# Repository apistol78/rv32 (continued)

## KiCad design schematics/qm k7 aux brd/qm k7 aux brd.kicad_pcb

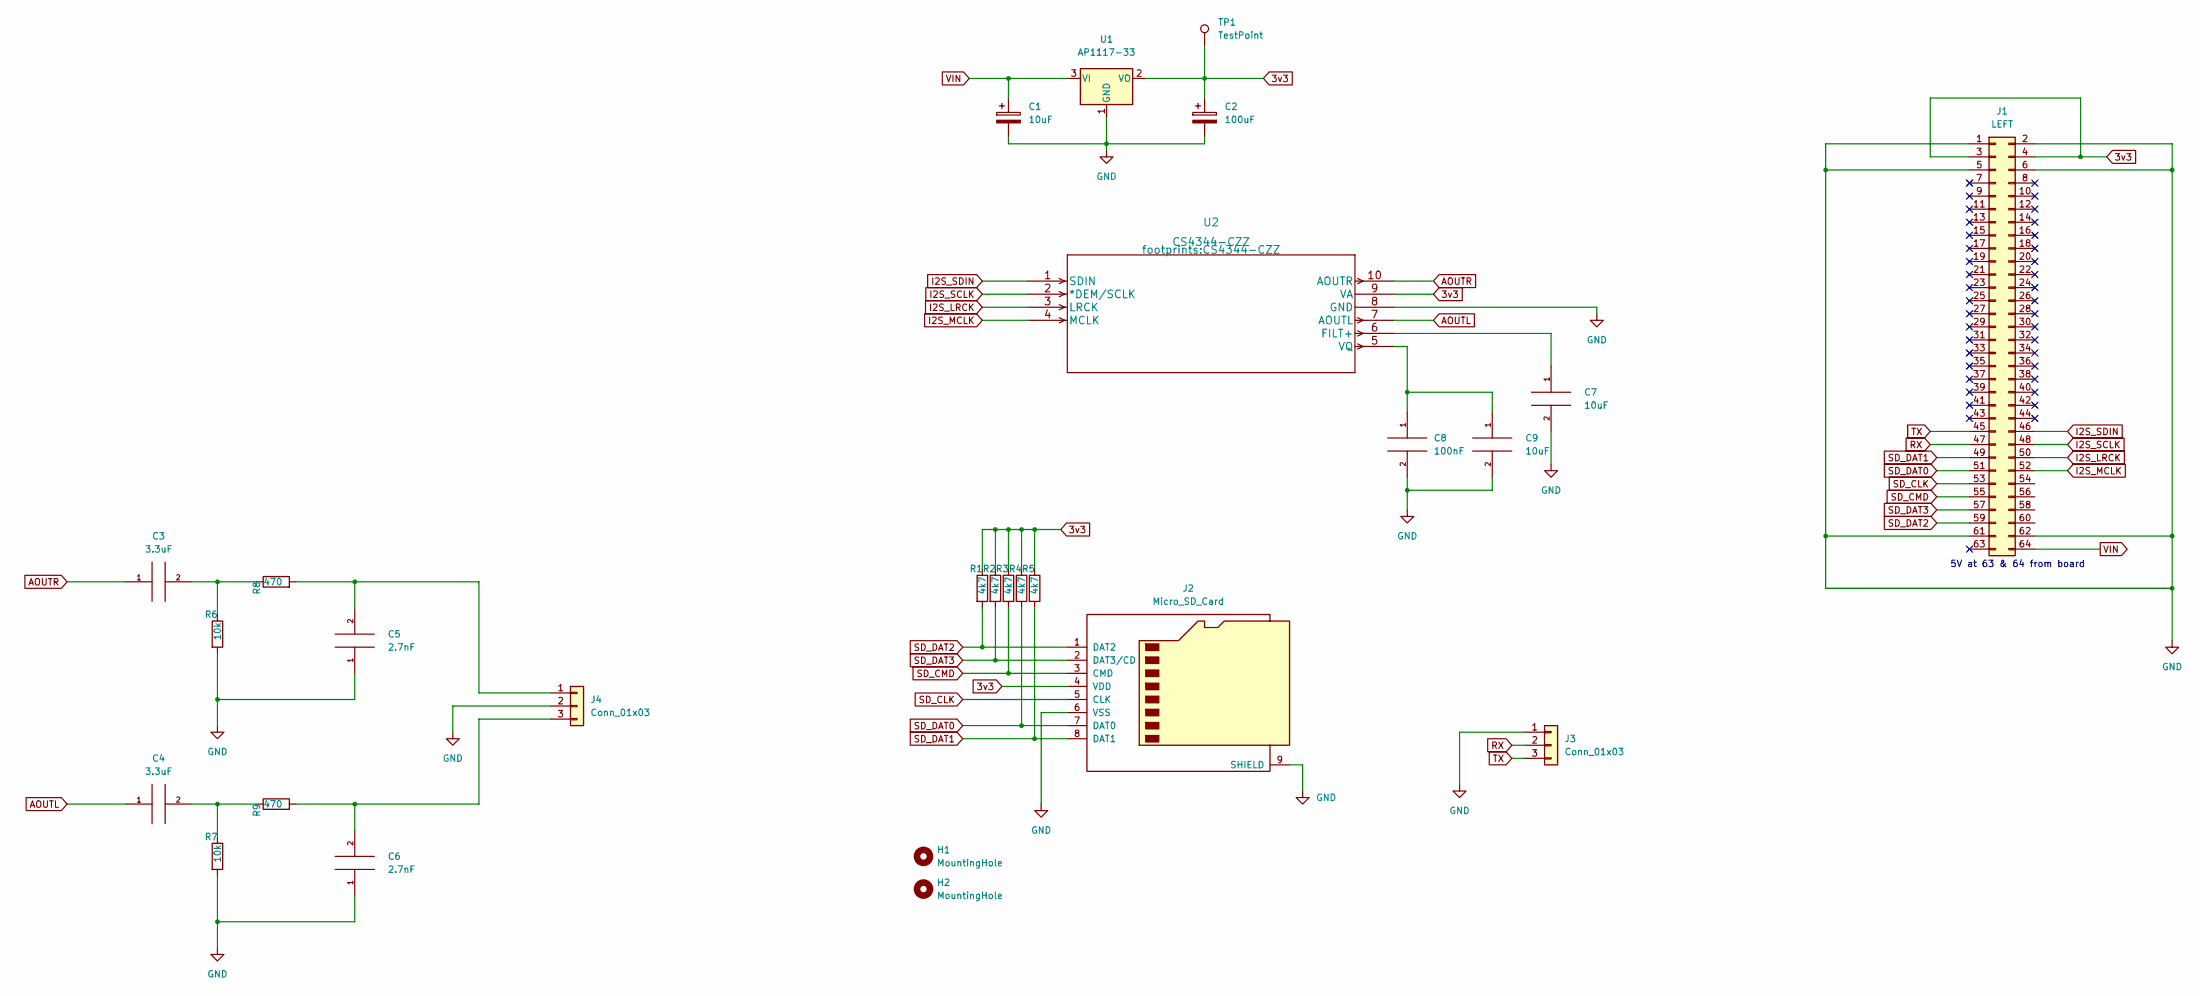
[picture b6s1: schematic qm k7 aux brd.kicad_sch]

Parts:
C1: 10uF; CP_Elec_5x5.3
C2: 100uF; CP_Elec_5x5.3
C3, C4: 3.3uF; C_0805_2012Metric_Pad1.18x1.45mm_HandSolder
C5, C6: 2.7nF; C_0805_2012Metric_Pad1.18x1.45mm_HandSolder
C7, C9: 10uF; C_0805_2012Metric_Pad1.18x1.45mm_HandSolder
C8: 100nF; C_0805_2012Metric_Pad1.18x1.45mm_HandSolder
H1, H2: MountingHole; MountingHole_3.2mm_M3_DIN965_Pad
J1: LEFT; PinSocket_2x32_P2.54mm_Vertical
J2: Micro_SD_Card; microSD_HC_Hirose_DM3D-SF
J3, J4: Conn_01x03; PinHeader_1x03_P2.54mm_Vertical
R1, R2, R3, R4, R5: 4k7; R_0805_2012Metric_Pad1.20x1.40mm_HandSolder
R6, R7: 10k; R_0805_2012Metric_Pad1.20x1.40mm_HandSolder
R8, R9: 470; R_0805_2012Metric_Pad1.20x1.40mm_HandSolder
TP1: TestPoint; TestPoint_Pad_D2.5mm
U1: AP1117-33; SOT-223-3_TabPin2
U2: CS4344-CZZ

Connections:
3v3: C2.1, J1.3, J1.4, J2.4 (VDD), R1.1, R2.1, R3.1, R4.1, R5.1, TP1.1, U1.2 (VO), U2.9 (VA)
AOUTL: C4.1, U2.7 (AOUTL)
AOUTR: C3.1, U2.10 (AOUTR)
GND: C1.2, C2.2, C5.1, C6.1, C7.2, C8.2, C9.2, J1.1, J1.2, J1.5, J1.6, J1.61, J1.62, J2.6 (VSS), J2.9 (SHIELD), J3.1, J4.2, R6.2, R7.2, U1.1 (GND), U2.8 (GND)
I2S_LRCK: J1.50, U2.3 (LRCK)
I2S_MCLK: J1.52, U2.4 (MCLK)
I2S_SCLK: J1.48, U2.2 (*DEM/SCLK)
I2S_SDIN: J1.46, U2.1 (SDIN)
unnamed: C3.2, R6.1, R8.1
unnamed: C4.2, R7.1, R9.1
unnamed: C5.2, J4.1, R8.2
unnamed: C6.2, J4.3, R9.2
unnamed: C7.1, U2.6 (FILT+)
unnamed: C8.1, C9.1, U2.5 (VQ)
RX: J1.47, J3.2
SD_CLK: J1.53, J2.5 (CLK)
SD_CMD: J1.55, J2.3 (CMD), R3.2
SD_DAT0: J1.51, J2.7 (DAT0), R4.2
SD_DAT1: J1.49, J2.8 (DAT1), R5.2
SD_DAT2: J1.59, J2.1 (DAT2), R1.2
SD_DAT3: J1.57, J2.2 (DAT3/CD), R2.2
TX: J1.45, J3.3
VIN: C1.1, J1.64, U1.3 (VI)

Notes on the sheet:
5V at 63 & 64 from board

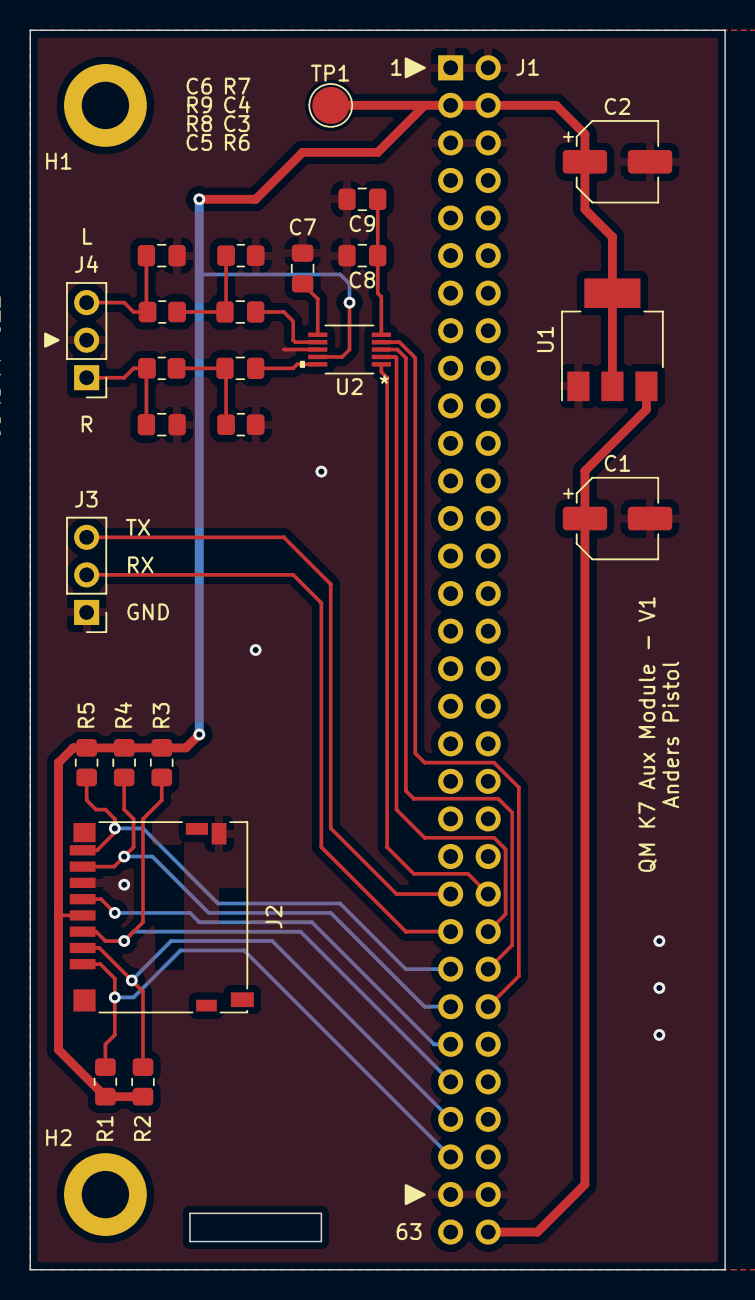
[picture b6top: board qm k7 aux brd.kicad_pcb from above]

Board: 2 copper layers, 47.0 x 83.8 mm, 27 parts (1 on the bottom side), 23 nets.

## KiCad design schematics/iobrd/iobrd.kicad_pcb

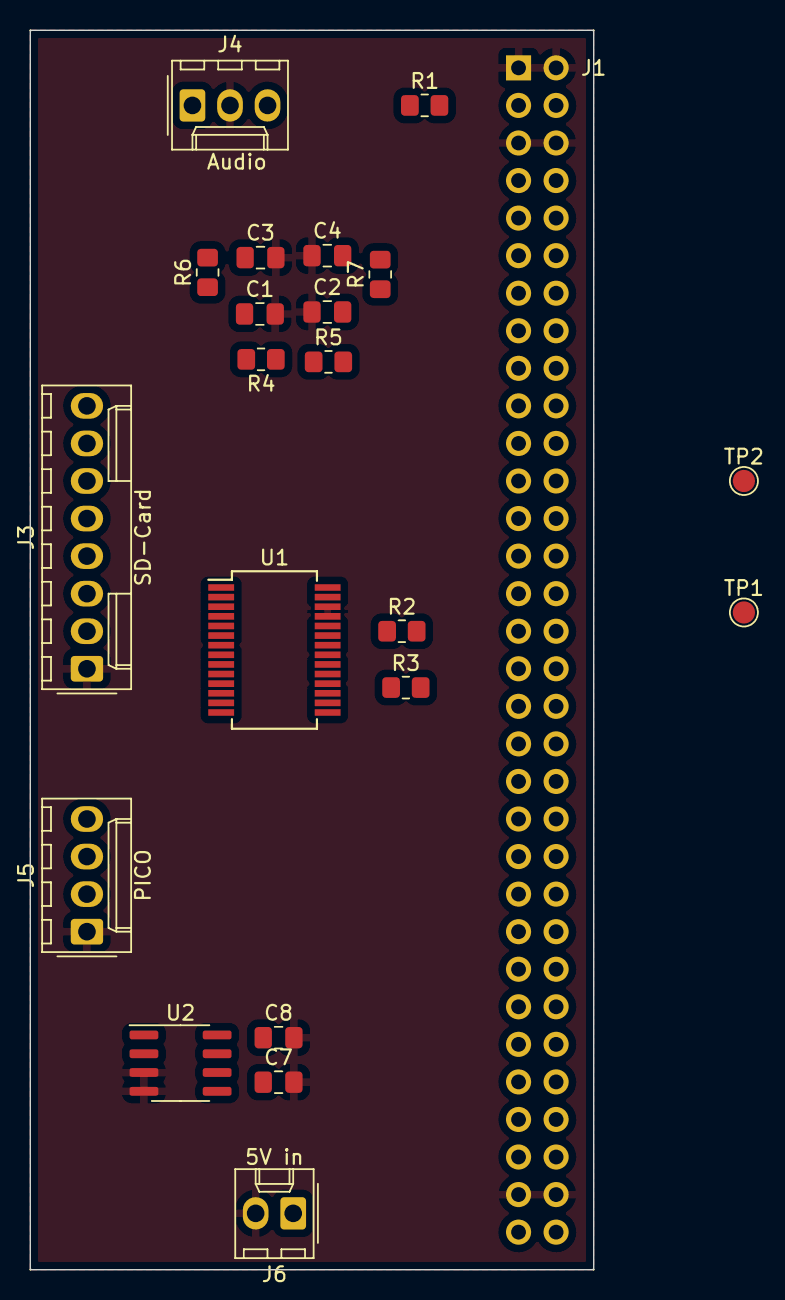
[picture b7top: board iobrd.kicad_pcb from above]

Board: 2 copper layers, 38.1 x 83.8 mm, 22 parts (1 on the bottom side), 24 nets, no tracks yet.

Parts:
C1, C2, C3, C4: 10nF; C_0805_2012Metric_Pad1.18x1.45mm_HandSolder
C7: 0.1uF; C_0805_2012Metric_Pad1.18x1.45mm_HandSolder
C8: 2.2uF; C_0805_2012Metric_Pad1.18x1.45mm_HandSolder
J1: Conn_02x32_Odd_Even; PinSocket_2x32_P2.54mm_Vertical
J3: Conn_01x08_Male; Molex_KK-254_AE-6410-08A_1x08_P2.54mm_Vertical
J4: Conn_01x03_Male; Molex_KK-254_AE-6410-03A_1x03_P2.54mm_Vertical
J5: Conn_01x04_Male; Molex_KK-254_AE-6410-04A_1x04_P2.54mm_Vertical
J6: Conn_01x02_Male; Molex_KK-254_AE-6410-02A_1x02_P2.54mm_Vertical
R1, R2, R3: 0; R_0805_2012Metric_Pad1.20x1.40mm_HandSolder
R4, R5, R6, R7: 560; R_0805_2012Metric_Pad1.20x1.40mm_HandSolder
TP1: 5v0; TestPoint_Pad_D1.5mm
TP2: 3v3; TestPoint_Pad_D1.5mm
U1: FT232RL; SSOP-28_5.3x10.2mm_P0.65mm
U2: LP2951-3.3_SOIC; SOIC-8_3.9x4.9mm_P1.27mm

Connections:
5v0: J1.63, J1.64, TP1.1
/3v3: C7.1, C8.1, J3.8, J5.4, R1.2, TP2.1, U2.1 (OUT), U2.2 (SENSE)
/AUDIO_PWM_L: J1.49, R4.1
/AUDIO_PWM_R: J1.51, R5.1
/PICO_RX: J1.46, J5.3
/PICO_TX: J1.48, J5.2
/RX: J1.45, U1.5 (RXD)
/SD_CLK: J1.53, J3.7
/SD_CMD: J1.55, J3.6
/SD_DAT0: J1.57, J3.5
/SD_DAT1: J1.59, J3.4
/SD_DAT2: J1.58, J3.3
/SD_DAT3: J1.60, J3.2
/TX: J1.47, U1.1 (TXD)
GND: C1.2, C2.1, C3.2, C4.1, C7.2, C8.2, J1.1, J1.2, J1.5, J1.6, J1.61, J1.62, J3.1, J4.2, J5.1, J6.2, U1.7 (GND), U1.18 (GND), U1.21 (GND), U1.25 (AGND), U1.26 (TEST), U2.3 (SHUTDOWN), U2.4 (GND)
unnamed: C1.1, R4.2, R6.1
unnamed: C2.2, R5.2, R7.1
unnamed: C3.1, R6.2
unnamed: C4.2, R7.2
unnamed: J1.3, J1.4, R1.1
unnamed: R2.1, U1.23 (CBUS0)
unnamed: R3.1, U1.22 (CBUS1)
unnamed: U2.6 (VTAP), U2.7 (FEEDBACK)
VIN: J6.1, U2.8 (IN)

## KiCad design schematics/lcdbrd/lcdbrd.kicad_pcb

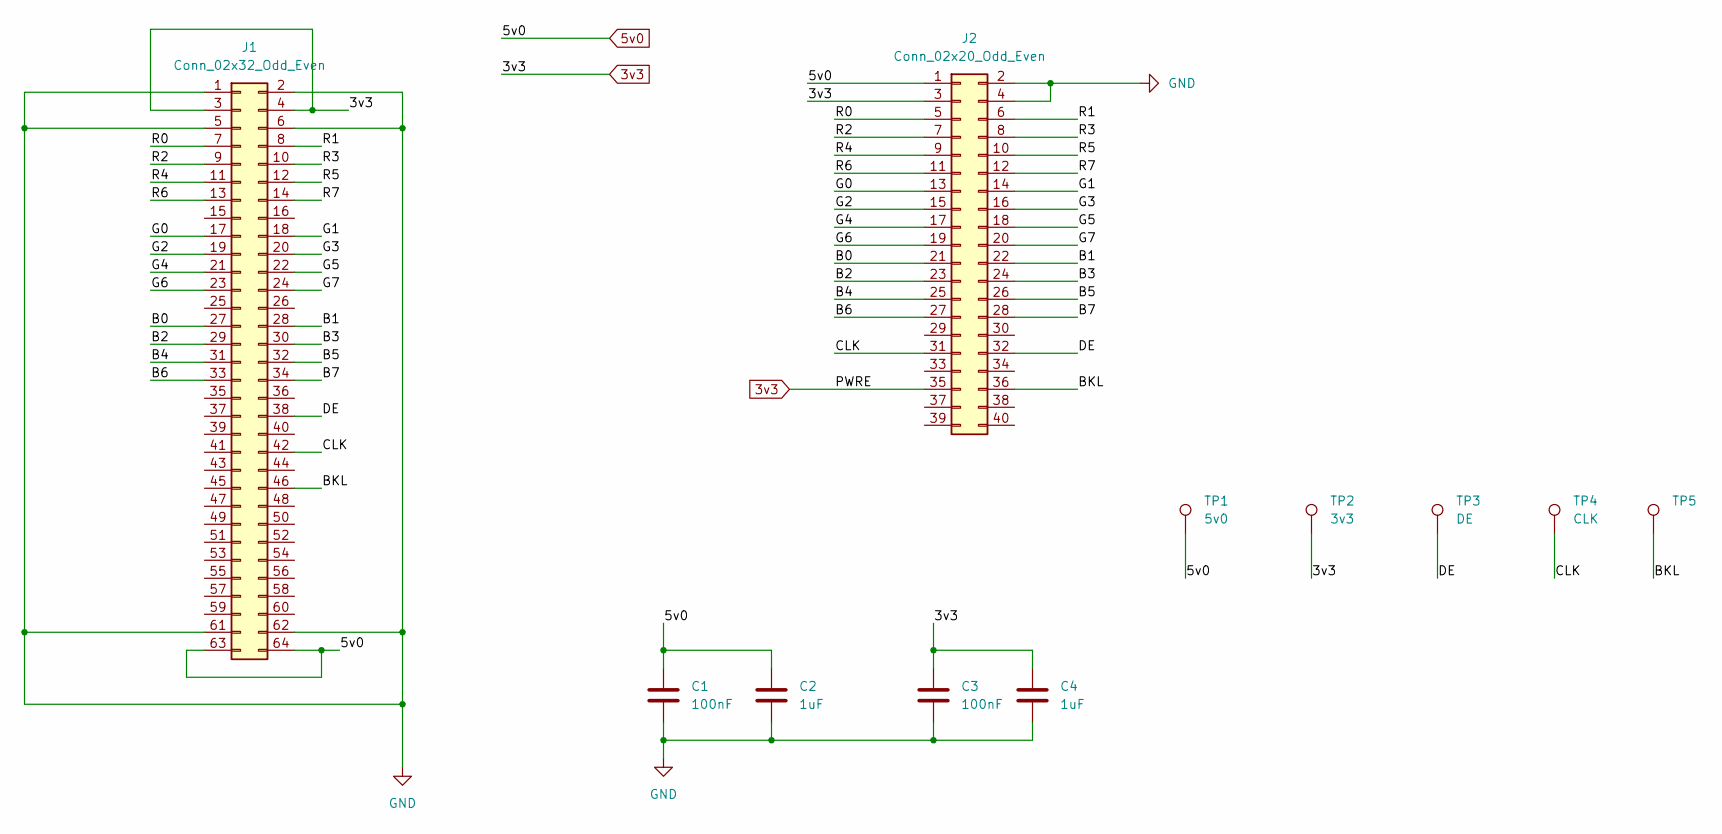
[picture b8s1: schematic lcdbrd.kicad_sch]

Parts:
C1, C3: 100nF; C_0805_2012Metric_Pad1.18x1.45mm_HandSolder
C2, C4: 1uF; C_0805_2012Metric_Pad1.18x1.45mm_HandSolder
J1: Conn_02x32_Odd_Even; PinSocket_2x32_P2.54mm_Vertical
J2: Conn_02x20_Odd_Even; IDC-Header_2x20_P2.54mm_Vertical
TP1: 5v0; TestPoint_Pad_D1.5mm
TP2: 3v3; TestPoint_Pad_D1.5mm
TP3: DE; TestPoint_Pad_D1.5mm
TP4: CLK; TestPoint_Pad_D1.5mm
TP5: (no value)

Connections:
3v3: C3.1, C4.1, J1.3, J1.4, J2.3, J2.35, TP2.1
5v0: C1.1, C2.1, J1.63, J1.64, J2.1, TP1.1
/B0: J1.27, J2.21
/B1: J1.28, J2.22
/B2: J1.29, J2.23
/B3: J1.30, J2.24
/B4: J1.31, J2.25
/B5: J1.32, J2.26
/B6: J1.33, J2.27
/B7: J1.34, J2.28
/BKL: J1.46, J2.36, TP5.1
/CLK: J1.42, J2.31, TP4.1
/DE: J1.38, J2.32, TP3.1
/G0: J1.17, J2.13
/G1: J1.18, J2.14
/G2: J1.19, J2.15
/G3: J1.20, J2.16
/G4: J1.21, J2.17
/G5: J1.22, J2.18
/G6: J1.23, J2.19
/G7: J1.24, J2.20
/R0: J1.7, J2.5
/R1: J1.8, J2.6
/R2: J1.9, J2.7
/R3: J1.10, J2.8
/R4: J1.11, J2.9
/R5: J1.12, J2.10
/R6: J1.13, J2.11
/R7: J1.14, J2.12
GND: C1.2, C2.2, C3.2, C4.2, J1.1, J1.2, J1.5, J1.6, J1.61, J1.62, J2.2, J2.4

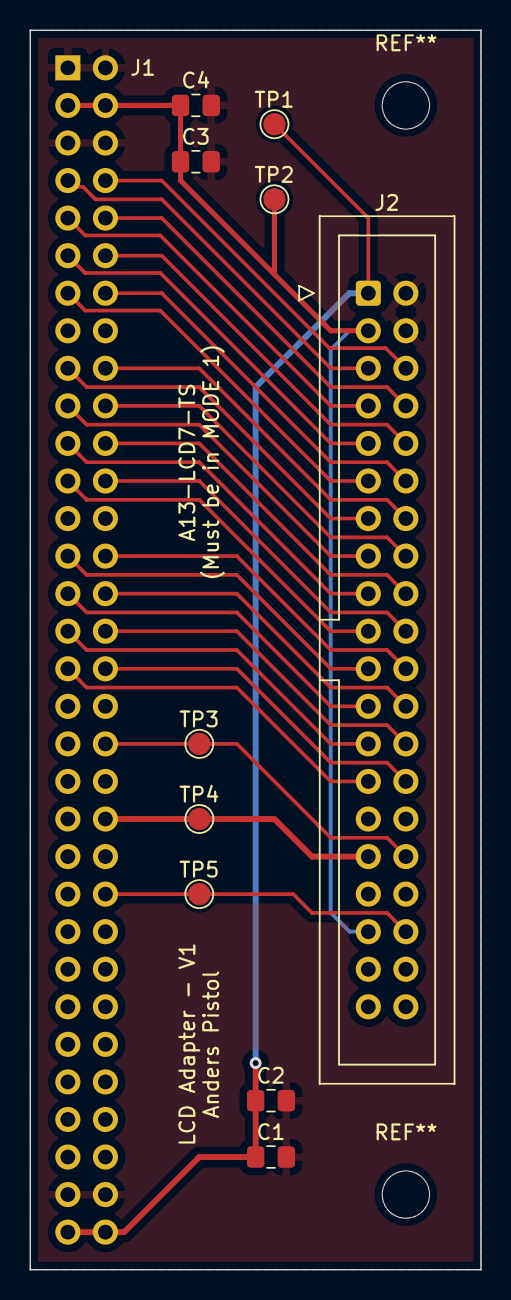
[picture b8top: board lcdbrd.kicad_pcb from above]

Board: 2 copper layers, 30.5 x 83.8 mm, 11 parts (1 on the bottom side), 30 nets.

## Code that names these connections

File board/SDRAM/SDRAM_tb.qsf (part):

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set_location_assignment PIN_AA13 -to sd_dat[2]
set_location_assignment PIN_Y15 -to sd_dat[1]
set_location_assignment PIN_Y14 -to sd_dat[0]
set_location_assignment PIN_AA15 -to sd_clk
set_location_assignment PIN_AB15 -to sd_cmd
set_location_assignment PIN_P16 -to sram_a[17]
set_location_assignment PIN_N21 -to sram_a[16]
set_location_assignment PIN_N20 -to sram_a[15]
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set_location_assignment PIN_V21 -to sram_a[2]
set_location_assignment PIN_U22 -to sram_a[1]
set_location_assignment PIN_W19 -to sram_a[0]
set_location_assignment PIN_W22 -to sram_ce_n
set_location_assignment PIN_AA20 -to sram_d[15]
set_location_assignment PIN_L19 -to sram_d[14]
set_location_assignment PIN_L18 -to sram_d[13]
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set_location_assignment PIN_U21 -to sram_d[2]
set_location_assignment PIN_U20 -to sram_d[1]
set_location_assignment PIN_V20 -to sram_d[0]
set_location_assignment PIN_N19 -to sram_lb_n
set_location_assignment PIN_M20 -to sram_oe_n
set_location_assignment PIN_M21 -to sram_ub_n
set_location_assignment PIN_Y22 -to sram_we_n
set_location_assignment PIN_AB17 -to uart_0_rx
set_location_assignment PIN_AB18 -to uart_0_tx
set_location_assignment PIN_N1 -to hdmi_sda
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set_location_assignment PIN_B7 -to hdmi_r[4]
set_location_assignment PIN_A7 -to hdmi_r[1]
set_location_assignment PIN_A8 -to hdmi_r[2]
set_location_assignment PIN_A9 -to hdmi_de
set_location_assignment PIN_A10 -to hdmi_r[0]
set_location_assignment PIN_B10 -to hdmi_vsync
set_location_assignment PIN_C9 -to hdmi_hsync
set_location_assignment PIN_G10 -to hdmi_sdo
set_location_assignment PIN_F10 -to hdmi_mclk
set_location_assignment PIN_C11 -to hdmi_sck
set_location_assignment PIN_B11 -to hdmi_ws
set_location_assignment PIN_B12 -to hdmi_nreset
set_location_assignment PIN_A12 -to hdmi_int
set_location_assignment PIN_B15 -to uart_1_rx
set_location_assignment PIN_C16 -to uart_1_tx
set_location_assignment PIN_Y16 -to audio_pwm_left
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
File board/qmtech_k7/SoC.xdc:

# create async clock groups from system clock and video clock.
#set_clock_groups -asynchronous -group [get_clocks {pll_clk|ip_pll_clk_inst|altera_pll_i|general[0].gpll~PLL_OUTPUT_COUNTER|divclk}] -group [get_clocks {pll_clk|ip_pll_clk_inst|altera_pll_i|general[2].gpll~PLL_OUTPUT_COUNTER|divclk}]
set_false_path -from [get_clocks -of_objects [get_pins ipclk/inst/mmcm_adv_inst/CLKOUT2]] -to [get_clocks -of_objects [get_pins ipclk/inst/mmcm_adv_inst/CLKOUT0]]

# UART FTDI
set_property IOSTANDARD LVCMOS33 [get_ports {uart_0_rx}]
set_property PACKAGE_PIN Y23 [get_ports {uart_0_rx}]
set_property IOSTANDARD LVCMOS33 [get_ports {uart_0_tx}]
set_property PACKAGE_PIN Y22 [get_ports {uart_0_tx}]

# UART IO
set_property IOSTANDARD LVCMOS33 [get_ports {uart_1_rx}]
set_property PACKAGE_PIN B26 [get_ports {uart_1_rx}]
set_property IOSTANDARD LVCMOS33 [get_ports {uart_1_tx}]
set_property PACKAGE_PIN C26 [get_ports {uart_1_tx}]

# SD
set_property IOSTANDARD LVCMOS33 [get_ports {sd_clk}]
set_property PACKAGE_PIN AE22 [get_ports {sd_clk}]
set_property IOSTANDARD LVCMOS33 [get_ports {sd_cmd}]
set_property PACKAGE_PIN AE23 [get_ports {sd_cmd}]
set_property IOSTANDARD LVCMOS33 [get_ports {sd_dat[0]}]
set_property PACKAGE_PIN AA25 [get_ports {sd_dat[0]}]
set_property IOSTANDARD LVCMOS33 [get_ports {sd_dat[1]}]
set_property PACKAGE_PIN AC23 [get_ports {sd_dat[1]}]
set_property IOSTANDARD LVCMOS33 [get_ports {sd_dat[2]}]
set_property PACKAGE_PIN AD26 [get_ports {sd_dat[2]}]
set_property IOSTANDARD LVCMOS33 [get_ports {sd_dat[3]}]
set_property PACKAGE_PIN AF24 [get_ports {sd_dat[3]}]

# I2S
set_property IOSTANDARD LVCMOS33 [get_ports {i2s_sdout}]
set_property PACKAGE_PIN AA22 [get_ports {i2s_sdout}]
set_property IOSTANDARD LVCMOS33 [get_ports {i2s_sclk}]
set_property PACKAGE_PIN AA24 [get_ports {i2s_sclk}]
set_property IOSTANDARD LVCMOS33 [get_ports {i2s_lrck}]
set_property PACKAGE_PIN AC24 [get_ports {i2s_lrck}]
set_property IOSTANDARD LVCMOS33 [get_ports {i2s_mclk}]
set_property PACKAGE_PIN AB25 [get_ports {i2s_mclk}]


#set_property IOSTANDARD LVCMOS33 [get_ports {led_1}]
#set_property PACKAGE_PIN B14 [get_ports {led_1}]
#set_property IOSTANDARD LVCMOS33 [get_ports {led_2}]
#set_property PACKAGE_PIN C14 [get_ports {led_2}]
#set_property IOSTANDARD LVCMOS33 [get_ports {led_3}]
#set_property PACKAGE_PIN E25 [get_ports {led_3}]

set_property IOSTANDARD LVCMOS33 [get_ports sys_rst]
set_property PACKAGE_PIN AB26 [get_ports sys_rst]

set_property IOSTANDARD LVCMOS33 [get_ports sys_clk]
set_property PACKAGE_PIN F22 [get_ports sys_clk]

# LCD

set_property IOSTANDARD LVCMOS33 [get_ports {hdmi_nreset}]
set_property PACKAGE_PIN C9 [get_ports {hdmi_nreset}]

set_property IOSTANDARD LVCMOS33 [get_ports {hdmi_sda}]
set_property PACKAGE_PIN D10 [get_ports {hdmi_sda}]
set_property IOSTANDARD LVCMOS33 [get_ports {hdmi_scl}]
set_property PACKAGE_PIN E10 [get_ports {hdmi_scl}]


set_property IOSTANDARD LVCMOS33 [get_ports {hdmi_idck}]
set_property PACKAGE_PIN D16 [get_ports {hdmi_idck}]

set_property IOSTANDARD LVCMOS33 [get_ports {hdmi_vsync}]
set_property PACKAGE_PIN B19 [get_ports {hdmi_vsync}]

set_property IOSTANDARD LVCMOS33 [get_ports {hdmi_hsync}]
set_property PACKAGE_PIN C19 [get_ports {hdmi_hsync}]

set_property IOSTANDARD LVCMOS33 [get_ports {hdmi_int}]
set_property PACKAGE_PIN A23 [get_ports {hdmi_int}]

set_property IOSTANDARD LVCMOS33 [get_ports {hdmi_de}]
set_property PACKAGE_PIN A19 [get_ports {hdmi_de}]

set_property IOSTANDARD LVCMOS33 [get_ports {hdmi_sdo}]
set_property PACKAGE_PIN A20 [get_ports {hdmi_sdo}]
set_property IOSTANDARD LVCMOS33 [get_ports {hdmi_sck}]
set_property PACKAGE_PIN D20 [get_ports {hdmi_sck}]
set_property IOSTANDARD LVCMOS33 [get_ports {hdmi_mclk}]
set_property PACKAGE_PIN B20 [get_ports {hdmi_mclk}]
set_property IOSTANDARD LVCMOS33 [get_ports {hdmi_ws}]
set_property PACKAGE_PIN D19 [get_ports {hdmi_ws}]


set_property PACKAGE_PIN A18 [get_ports {hdmi_r[0]}]
set_property PACKAGE_PIN C18 [get_ports {hdmi_r[1]}]
set_property PACKAGE_PIN C17 [get_ports {hdmi_r[2]}]
set_property PACKAGE_PIN D18 [get_ports {hdmi_r[3]}]
set_property PACKAGE_PIN E18 [get_ports {hdmi_r[4]}]
set_property PACKAGE_PIN A17 [get_ports {hdmi_r[5]}]
set_property PACKAGE_PIN B17 [get_ports {hdmi_r[6]}]
set_property PACKAGE_PIN B16 [get_ports {hdmi_r[7]}]

set_property PACKAGE_PIN C16 [get_ports {hdmi_g[0]}]
set_property PACKAGE_PIN D15 [get_ports {hdmi_g[1]}]
set_property PACKAGE_PIN A15 [get_ports {hdmi_g[2]}]
set_property PACKAGE_PIN B15 [get_ports {hdmi_g[3]}]
set_property PACKAGE_PIN C13 [get_ports {hdmi_g[4]}]
set_property PACKAGE_PIN C14 [get_ports {hdmi_g[5]}]
set_property PACKAGE_PIN A14 [get_ports {hdmi_g[6]}]
set_property PACKAGE_PIN B14 [get_ports {hdmi_g[7]}]

set_property PACKAGE_PIN D13 [get_ports {hdmi_b[0]}]
set_property PACKAGE_PIN D14 [get_ports {hdmi_b[1]}]
set_property PACKAGE_PIN A12 [get_ports {hdmi_b[2]}]
set_property PACKAGE_PIN A13 [get_ports {hdmi_b[3]}]
set_property PACKAGE_PIN C11 [get_ports {hdmi_b[4]}]
set_property PACKAGE_PIN C12 [get_ports {hdmi_b[5]}]
set_property PACKAGE_PIN B11 [get_ports {hdmi_b[6]}]
set_property PACKAGE_PIN B12 [get_ports {hdmi_b[7]}]

set_property IOSTANDARD LVCMOS33 [get_ports {hdmi_r[0]}]
set_property IOSTANDARD LVCMOS33 [get_ports {hdmi_r[1]}]
set_property IOSTANDARD LVCMOS33 [get_ports {hdmi_r[2]}]
set_property IOSTANDARD LVCMOS33 [get_ports {hdmi_r[3]}]
set_property IOSTANDARD LVCMOS33 [get_ports {hdmi_r[4]}]
set_property IOSTANDARD LVCMOS33 [get_ports {hdmi_r[5]}]
set_property IOSTANDARD LVCMOS33 [get_ports {hdmi_r[6]}]
set_property IOSTANDARD LVCMOS33 [get_ports {hdmi_r[7]}]

set_property IOSTANDARD LVCMOS33 [get_ports {hdmi_g[0]}]
set_property IOSTANDARD LVCMOS33 [get_ports {hdmi_g[1]}]
set_property IOSTANDARD LVCMOS33 [get_ports {hdmi_g[2]}]
set_property IOSTANDARD LVCMOS33 [get_ports {hdmi_g[3]}]
set_property IOSTANDARD LVCMOS33 [get_ports {hdmi_g[4]}]
set_property IOSTANDARD LVCMOS33 [get_ports {hdmi_g[5]}]
set_property IOSTANDARD LVCMOS33 [get_ports {hdmi_g[6]}]
set_property IOSTANDARD LVCMOS33 [get_ports {hdmi_g[7]}]

set_property IOSTANDARD LVCMOS33 [get_ports {hdmi_b[0]}]
set_property IOSTANDARD LVCMOS33 [get_ports {hdmi_b[1]}]
set_property IOSTANDARD LVCMOS33 [get_ports {hdmi_b[2]}]
set_property IOSTANDARD LVCMOS33 [get_ports {hdmi_b[3]}]
set_property IOSTANDARD LVCMOS33 [get_ports {hdmi_b[4]}]
set_property IOSTANDARD LVCMOS33 [get_ports {hdmi_b[5]}]
set_property IOSTANDARD LVCMOS33 [get_ports {hdmi_b[6]}]
set_property IOSTANDARD LVCMOS33 [get_ports {hdmi_b[7]}]

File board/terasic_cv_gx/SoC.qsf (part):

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set_location_assignment PIN_J10 -to LEDR[9]
set_location_assignment PIN_V6 -to REFCLK_p0
set_location_assignment PIN_N7 -to REFCLK_p1
set_location_assignment PIN_AB6 -to SD_CLK
set_location_assignment PIN_W8 -to SD_CMD
set_location_assignment PIN_U7 -to SD_DAT[0]
set_location_assignment PIN_T7 -to SD_DAT[1]
set_location_assignment PIN_V8 -to SD_DAT[2]
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set_location_assignment PIN_J26 -to SRAM_A[15]
set_location_assignment PIN_N24 -to SRAM_A[16]
set_location_assignment PIN_M24 -to SRAM_A[17]
set_location_assignment PIN_N23 -to SRAM_CE_n
set_location_assignment PIN_E24 -to SRAM_D[0]
set_location_assignment PIN_E25 -to SRAM_D[1]
set_location_assignment PIN_K24 -to SRAM_D[2]
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set_location_assignment PIN_G22 -to SRAM_D[13]
set_location_assignment PIN_L22 -to SRAM_D[14]
set_location_assignment PIN_K21 -to SRAM_D[15]
set_location_assignment PIN_H25 -to SRAM_LB_n
set_location_assignment PIN_M22 -to SRAM_OE_n
set_location_assignment PIN_M25 -to SRAM_UB_n
set_location_assignment PIN_G25 -to SRAM_WE_n
set_location_assignment PIN_AC9 -to SW[0]
set_location_assignment PIN_AE10 -to SW[1]
set_location_assignment PIN_AD13 -to SW[2]
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set_location_assignment PIN_AC10 -to SW[7]
set_location_assignment PIN_Y11 -to SW[8]
set_location_assignment PIN_AE19 -to SW[9]
set_location_assignment PIN_M9 -to UART_RX
set_location_assignment PIN_L9 -to UART_TX
set_global_assignment -name STRATIX_DEVICE_IO_STANDARD "2.5 V"
set_global_assignment -name MIN_CORE_JUNCTION_TEMP 0
set_global_assignment -name MAX_CORE_JUNCTION_TEMP 85
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
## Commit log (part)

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2022-02-14 Rv32: FPU working, still needs ton of optimizations.
2022-02-15 Rv32: Implemented min/max float instructions.
2022-02-15 Rv32: Implemented unsigned int to float conversion.
2022-02-15 Rv32: Changed back to O3. Also improved min/max verify tests.
2022-02-15 Rv32: Updated Quartus project.
2022-02-15 Rv32: Optimized one cycle from each add, mul and float to int instructions.
2022-02-16 Rv32: Some experiments with memory setup, was able to slight optimize icache fetch.
2022-02-22 Rv32: Some minor updates to GtkWave save file etc.
2022-02-23 Rv32: Merged BRAM modules, using parameters to generate permutations.
2022-02-23 Rv32: Removed old BRAM modules.
2022-02-23 Rv32: Stubbed a PLIC peripherial, not tested.
2022-02-23 Rv32: Added qmtech cv board project, CPU running at 50 MHz with smaller caches. No peripherials.
2022-02-24 Rv32: FPU min/max bug with result not being latched properly due to multicycle op.
2022-02-25 Rv32: Fixed issue where FPU instructions was started before previous memory op still busy.
2022-02-25 Rv32: Quartus projects updated.
2022-02-28 Rv32: BUS profiler implemented in Rv32T.
2022-02-28 Rv32: Forgot some files in Rv32T.
2022-03-02 Rv32: SDRAM controller implemented in QM-Tech board.
2022-03-04 Rv32: MT kernel implemented in Runtime.
2022-03-04 Rv32: Added REG parameter to BusAccess.
2022-03-08 Rv32: Able to use combinatorial BusAccess, not used in HW since it causes major timing issues.
2022-03-08 Rv32: Seems to be some issue with initialized globals, ensure kernel variables are initialized by code for now.
2022-03-09 Rv32: Worked on interrupts and MT kernel. Still issues prob were timer reenters ecall interrupts.
2022-03-10 Rv32: Always use signed sum result from ALU for JUMP and MEM instructions, should improve timing on those paths.
2022-03-10 Rv32: SDRAM updated. Optimized timing on forwards.
2022-03-12 Rv32: Some work, added audio to Terasic board etc.
2022-03-15 Rv32: Using generate to enable/disable dcache in mem stage. Remapped op codes.
2022-03-16 Rv32: SPI LCD display working.
2022-03-17 Rv32: Some schematics work.
2022-03-18 Rv32: Able to generate an vmem-range file which define necessary range of an binary.
2022-03-22 Rv32: Kernal application added.
2022-03-22 Rv32: Removed kernel from Runtime, will be impl in Kernal.
2022-03-23 Rv32: At070TN92 video signal generator, added to QMTech CV board.
2022-03-23 Rv32: LCD adapter board schematics added (ordered).
2022-03-24 Rv32: Moved SDRAM interface module of terasic board into boards folder. Updated SoCs.
2022-03-25 Rv32: Improved video API in Runtime.
2022-03-27 Rv32: QMTech Kintex-7 board added.
2022-03-27 Rv32: Some cleanup in FIFO and UART.
2022-03-28 Rv32: Refactored video API a bit.
2022-03-29 Rv32: Some work on DDR3 interface.
2022-03-31 Rv32: Able to use DDR3 ram on K7.
2022-04-01 Rv32: icache and dcache uses ordinary BRAM and does initialization by them selves. This should improve timing but not verified yet.
2022-04-03 Rv32: Minor cleanup in Rv32T top.
2022-04-03 Rv32: Added some legend to LCD board schematics.
2022-04-05 Rv32: Added SRAM and SD schematic.
2022-04-06 Rv32: Updated SRAM brd schematic. Also updated legend in lcdbrd.
2022-04-11 Rv32: Some work on Terasic CV GX board, brought back into life. Also some reset logic fixes.
2022-04-11 Rv32: Added "busy" signals from BusAccess so we can monitor traffic, used to stall DMA when video is accessing VRAM.
2022-04-12 Rv32: SRAM Aux board schematics updated. JLCPCB v1
2022-04-15 Rv32: Added some legend to SRAM board schematics.
2022-04-15 Rv32: Fixed video in Rv32T.
2022-04-15 Rv32: Work on QM-tech K7 board, support for SD card, increased to 125 MHz etc.
2022-04-17 Rv32: Added a BRIDGE component to isolate peripherials from bus and thus improve timing. Fixed a lot ot issues with K7 board, able to use LRU cache to improve DDR3 access.
2022-04-20 Rv32: Implemented SD support in Rv32, able to run Doom again.
2022-04-21 Rv32: Terasic CV board updated using BRIDGE.
2022-04-24 Rv32: Updated Terasic CV board.
2022-04-24 Rv32: Some more cleanup from disabling FPU.
2022-04-25 Rv32: Minor cleanup in VIDEO_VGA.
2022-04-26 Rv32: Forgot to uncomment reset logic in caches. Also minor change i icache. Seems to improve timing also?
2022-04-27 Rv32: Able to control CPU/GPU read and write offsets in VMODE, no longer have to DMA frames.
2022-04-29 Rv32: Audio over I2S working.
2022-05-07 Rv32: Quartus compile issues fixed. Fixed non-registered mode on BusAccess.
2022-05-09 Rv32: Stubbed the SIL9024A HDMI initialization.
2022-05-09 Rv32: Registered icache implementation, currently misses everything.
2022-05-09 Rv32: Begun implementing UART RX device in Rv32T.
2022-05-10 Rv32: Implemented a write buffer to VMODE to queue vram writes. Also made BRIDGE partial combinatorial.
2022-05-20 Rv32: Added SHID firmware.
2022-05-22 Rv32: Video size in Rv32 emulator fixed.
2022-05-24 Rv32: Disabled CDC in SHID. Also cleaned up a bit.
2022-05-31 Rv32: Terasic board up and running again.
2022-06-02 Rv32: QM Tech CV board updated, video SRAM working and SHID.
2022-06-07 Rv32: Moved device ID and frequency registers from Timer to SystemRegisters.
2022-06-11 Rv32: Some work on USB HID board.
2022-06-15 Rv32: Implemented SystemRegisters in Rv32 emulator.
2022-06-17 Rv32: Re-enabled interrupts. Wired up audio HW interrupt on QM cyclone.
2022-06-17 Rv32: Some cleanup in Runtime. Added soft restart function.
2022-06-17 Rv32: Able to load and execute "boot.elf" from SD by firmware. No longer need block RAM, instead rely entirely on SDRAM.
2022-06-18 Rv32: Fixed default stack pointer in emulator. Also reduced video size to match HW.
2022-06-20 Rv32: Firmware using sysreg to determine stack location.
2022-06-21 Rv32: Cleaned up gitignore a bit.
2022-06-22 Rv32: Minor update to README and gitignore.
2022-06-22 Rv32: Font added.
2022-06-23 Rv32: Removed Kernal project.
2022-06-23 Rv32: Rv32T initial stack set similar to firmware.
2022-06-27 Rv32: Refactored Rv32 Bus interface, devices only need to implement 32-bit read/write methods.
2022-06-27 Rv32: More cleanup in Rv32 emulator.
2022-07-01 Rv32: Using case statement instead of multiple if-else in generated SV.
2022-07-06 Rv32: Fixed BRAM peripherials, was unable to infer block ram due to type changes.
2022-07-13 Rv32: Modified SHID to use another pin for LED; HID board working.
2022-07-13 Rv32: Begun implementing keyboard support in Rv32 emulator.
2022-07-19 Rv32: Re-enabled IRQ handling in CPU, and some minor cleanup. Launch script no longer have to specify initial stack since it's handled by firmware. CV2 SoC with positive slack.
2022-07-29 Rv32: Cleaned up SDRAM controller, less frequent refresh rate.
2022-07-29 Rv32: SDRAM controller configurable, able to specify user and sdram data widths and calculate burst lengths accordingly.
2022-08-03 Rv32: Added sysreg define for QMTech CV 5 board.
2022-08-08 Rv32: No longer check decode fault on HW due to timing.
2022-08-08 Rv32: Some fixes in VMODE when used with higher resolution modes.
2022-08-25 Rv32: Interrupts are working on HW, timer and audio interrupts tested. Implemented a "play" command in shell to play some music using interrupts.
2022-08-29 Rv32: Moved U32 read from UART into RT.
2022-08-29 Rv32: Added ScummVM port.
2022-08-30 Rv32: Logging of unaligned memory access in emulator.
2022-08-30 Rv32: Some improvements to sound in Scumm. Still very glitchy.
2022-09-04 Rv32: Some cleanup in CPU pipeline busy signals.
2022-09-04 Rv32: Kernel lock primitive implemented.
2022-09-06 Rv32: Another revision of the AUX board, ordered from JLCPCB.
2022-09-08 Rv32: Some cleanup, trying to figure out how to pass arguments to "processes".
2022-09-09 Rv32: Removed CPU_WriteBuffer since never been working.
2022-09-10 Rv32: 4-bit SD write working.
2022-09-12 Rv32: SD write support in emulator. Fixed browsing interface in ScummVM.
2022-09-13 Rv32: Write out audio from emulator.
2022-09-13 Rv32: Renamed VMODE_chunky to VIDEO_controller.
2022-09-13 Rv32: Renamed combinatorial icache/dcache modules.
2022-09-17 Rv32: Using Rev 2 of SRAM module in QMTech CV 2. Fixed a lot of other issues as well, video much improved etc.
2022-09-17 Rv32: Some optimizations in SD and IO code; read activity on first LED.
2022-09-18 Rv32: Increased UART 1 RX buffer size, was missing some input from HID. Added constants for file_seek.
2022-09-19 Rv32: Fixed HDMI device in Rv32T.
2022-09-21 Rv32: Missing CPU rdata from VIDEO_controller fixed when wbuffer is enabled.
2022-09-22 Rv32: Disabled accelerated SD reading in emulator.
2022-09-23 Rv32: Improved busy signal in execute stage.
2022-09-25 Rv32: Exposed some function keys from Rv32 emulator.
2022-09-26 Rv32: Kernel timeout signal.
2022-09-28 Rv32: Increased frequency of scheduler. Using CSR to trigg another interrupt when yield. Timer module has four channels.
2022-09-28 Rv32: Optimized Audio. Also some cleanup.
2022-09-28 Rv32: Timer interrupt pending instead of ignored when TIE disabled; still doesn't work and need verification.
2022-09-30 Rv32: More work on Kernel; fixed issues with MIE and MTIE, able to handle critical section quickly.
2022-10-03 Rv32: Improved icache (comb) a bit, no need for IDLE state.
2022-10-04 Rv32: Some optimizations to timer and kernel; using WFI in yield.
2022-10-04 Rv32: Updated readme, now in markdown.
2022-10-05 Rv32: Implemented "retired" CSR.
2022-10-11 Rv32: Fixed issues with kernel since rdtime change.
2022-10-11 Rv32: Removed "external interrupt enable" pin; was skipping vblanks.
2022-10-17 Rv32: Two modes of interrupts in Timer. Able to use countdown in Kernel.
2022-10-18 Rv32: Reduced buffer size in audio controller.
2022-10-19 Rv32: Added VS code tasks.
2022-10-23 Rv32: Reduced number of latency cycles in div/mul IPs. Disabled "wait" state in video controller. Tweaked kernel, respond faster to threads waiting on signals. Increased sampling rate in audio.
2022-10-24 Rv32: Rewrote icache, no longer require a stall signal, only "reg" is working atm.
2022-10-25 Rv32: Fixed bus profiler in Rv32T.
2022-10-26 Rv32: Reverted change in VIDEO controller. Added "full" signal from WriteBuffer.
2022-10-27 Rv32: Able to configure playback rate of audio through audio controller.
2022-10-28 Rv32: Disabled warnings from SD initialization.
2022-10-31 Rv32: Tracking active row per bank in SDRAM controller (20->26 MiB/s write increase). Also able to specify default bootmode as a parameter to SystemRegisters.
2022-10-31 Rv32: Added a memtest to Boot to measure memory.
2022-10-31 Rv32: Dumping some more registers when exiting Rv32T.
2022-11-01 Rv32: Fix in comb D$ for flush. Added "read offset" register to Video controller, will copy entire frame before presenting to reduce tearing.
2022-11-03 Rv32: Able to select between one-way or two-way associative icache in emulator.
2022-11-04 Rv32: Yield thread when raising signal.
2022-11-07 Rv32: Verify up and running again.
2022-11-09 Rv32: Some cleanup in emulator.
2022-11-15 Rv32: Removed CV legend schematic; no longer relevant.
2022-11-22 Rv32: 4 different video modes implemented.
2023-01-15 Rv32: Forgot to remove comment in VIDEO_controller. Verified and delay necessary.
2023-01-15 Rv32: Added a frame counter to Rv32T.
2023-01-17 Rv32: Delayed HDMI signals to improve timing; only in sim atm.
2023-01-17 Rv32: Added the video delay to HW, seems to work.
2023-01-19 Rv32: Able to change vram read offset mid frame.
2023-01-20 Rv32: Increased duration of vsync and hsync in VGA generator.
2023-01-20 Rv32: DualPort is now combinatorial, saves some cycles. Fixed video issues; video fully correct now on HW.
2023-01-23 Rv32: SRAM stable at 6 cycles.
2023-01-31 Rv32: Some drawing optimization in Doom, able to shave of memory access in inner loop due to aliasing rules.
2023-03-04 Rv32: Cleanup kernel threads when shutting down Console.
2023-03-15 Rv32: Added MPL license notice on relevant files.
